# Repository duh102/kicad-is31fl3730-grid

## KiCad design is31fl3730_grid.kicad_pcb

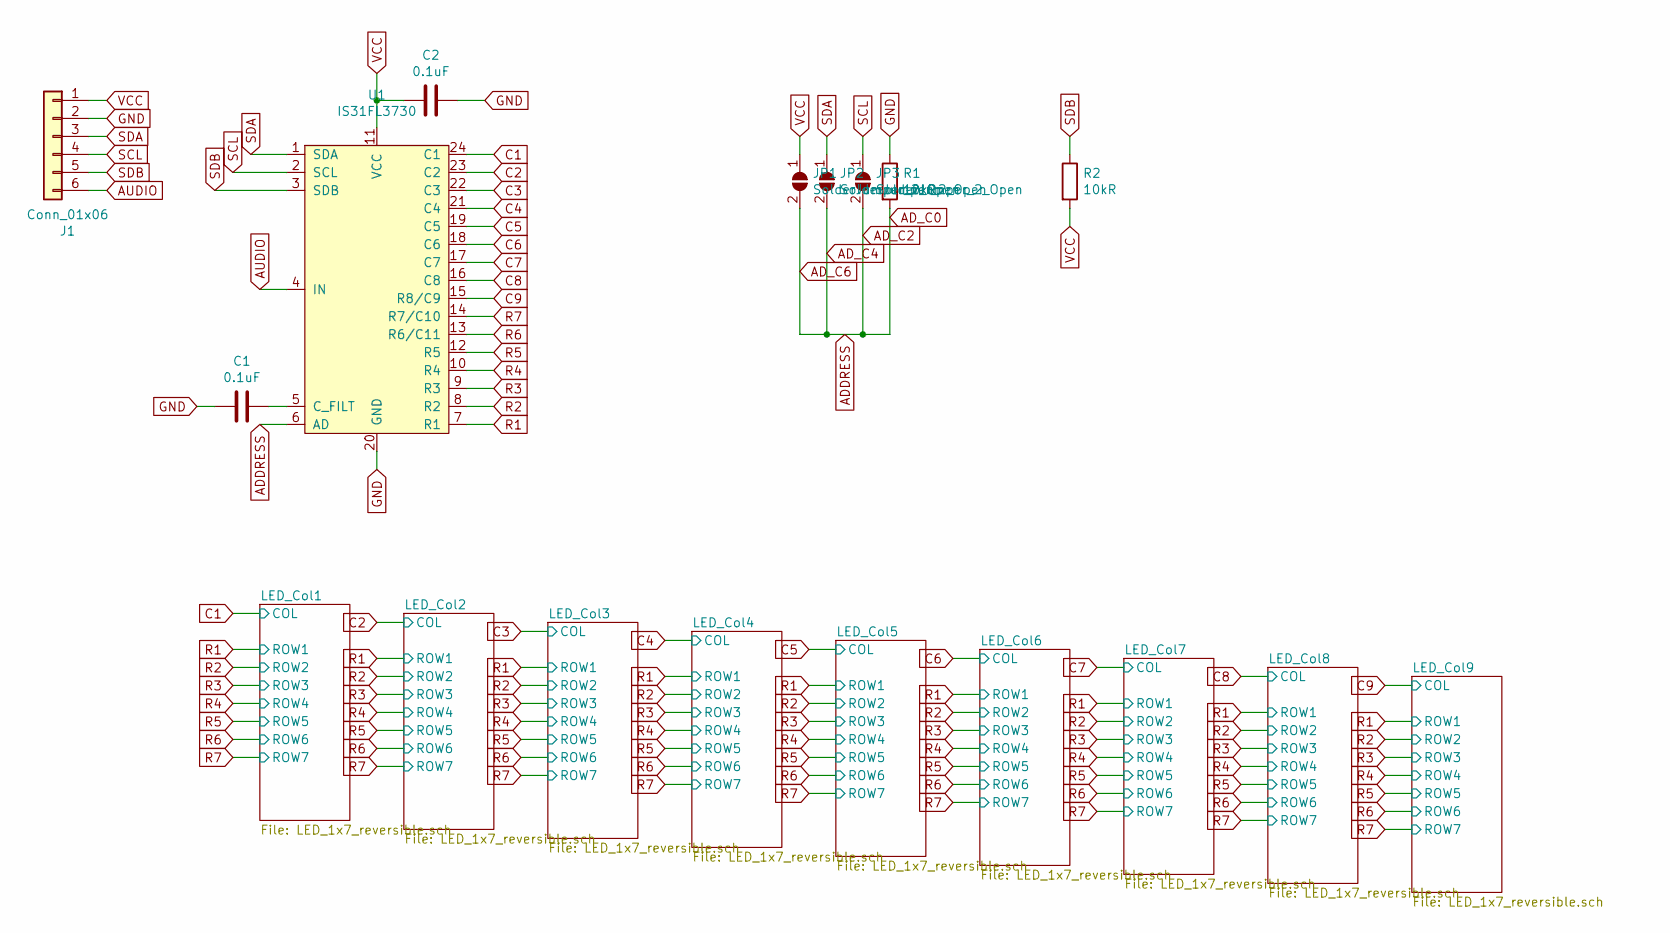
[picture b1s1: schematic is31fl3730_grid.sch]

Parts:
C1, C2: 0.1uF; C_0603_1608Metric
J1: Conn_01x06; PinHeader_1x06_P2.54mm_Vertical
JP1, JP2, JP3: SolderJumper_2_Open; SolderJumper-2_P1.3mm_Open_TrianglePad1.0x1.5mm
R1, R2: 10kR; R_0805_2012Metric
U1: IS31FL3730; QFN-24-1EP_4x4mm_P0.5mm_EP2.8x2.8mm

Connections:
ADDRESS: JP1.2 (B), JP2.2 (B), JP3.2 (B), R1.2, U1.6 (AD)
AUDIO: J1.6, U1.4 (IN)
C1: U1.24 (C1); also elsewhere on the board
C2: U1.23 (C2); also elsewhere on the board
C3: U1.22 (C3); also elsewhere on the board
C4: U1.21 (C4); also elsewhere on the board
C5: U1.19 (C5); also elsewhere on the board
C6: U1.18 (C6); also elsewhere on the board
C7: U1.17 (C7); also elsewhere on the board
C8: U1.16 (C8); also elsewhere on the board
C9: U1.15 (R8/C9); also elsewhere on the board
GND: C1.2, C2.1, J1.2, R1.1, U1.20 (GND)
unnamed: C1.1, U1.5 (C_FILT)
R1: U1.7 (R1); also elsewhere on the board
R2: U1.8 (R2); also elsewhere on the board
R3: U1.9 (R3); also elsewhere on the board
R4: U1.10 (R4); also elsewhere on the board
R5: U1.12 (R5); also elsewhere on the board
R6: U1.13 (R6/C11); also elsewhere on the board
R7: U1.14 (R7/C10); also elsewhere on the board
SCL: J1.4, JP3.1 (A), U1.2 (SCL)
SDA: J1.3, JP2.1 (A), U1.1 (SDA)
SDB: J1.5, R2.1, U1.3 (SDB)
VCC: C2.2, J1.1, JP1.1 (A), R2.2, U1.11 (VCC)

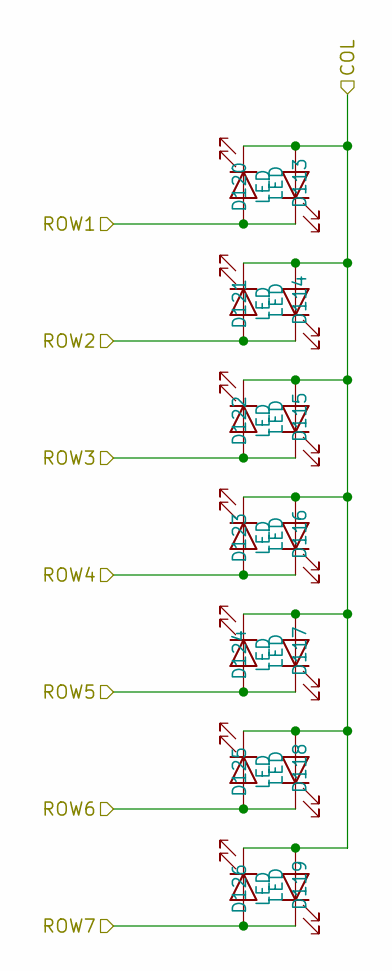
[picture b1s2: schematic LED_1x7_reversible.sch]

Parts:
D1, D2, D3, D4, D5, D6, D7, D8, D9, D10, D11, D12, D13, D14: LED; LED_0805_2012Metric

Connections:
C1: D1.1 (K), D2.1 (K), D3.1 (K), D4.1 (K), D5.1 (K), D6.1 (K), D7.1 (K), D8.2 (A), D9.2 (A), D10.2 (A), D11.2 (A), D12.2 (A), D13.2 (A), D14.2 (A); also elsewhere on the board
R1: D1.2 (A), D8.1 (K); also elsewhere on the board
R2: D2.2 (A), D9.1 (K); also elsewhere on the board
R3: D3.2 (A), D10.1 (K); also elsewhere on the board
R4: D4.2 (A), D11.1 (K); also elsewhere on the board
R5: D5.2 (A), D12.1 (K); also elsewhere on the board
R6: D6.2 (A), D13.1 (K); also elsewhere on the board
R7: D7.2 (A), D14.1 (K); also elsewhere on the board

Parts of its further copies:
D15, D16, D17, D18, D19, D20, D21, D22, D23, D24, D25, D26, D27, D28, D29, D30, D31, D32, D33, D34, D35, D36, D37, D38, D39, D40, D41, D42, D43, D44, D45, D46, D47, D48, D49, D50, D51, D52, D53, D54, D55, D56, D57, D58, D59, D60, D61, D62, D63, D64, D65, D66, D67, D68, D69, D70, D71, D72, D73, D74, D75, D76, D77, D78, D79, D80, D81, D82, D83, D84, D85, D86, D87, D88, D89, D90, D91, D92, D93, D94, D95, D96, D97, D98, D99, D100, D101, D102, D103, D104, D105, D106, D107, D108, D109, D110, D111, D112, D113, D114, D115, D116, D117, D118, D119, D120, D121, D122, D123, D124, D125, D126: LED; LED_0805_2012Metric

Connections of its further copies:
C2: D15.1 (K), D16.1 (K), D17.1 (K), D18.1 (K), D19.1 (K), D20.1 (K), D21.1 (K), D22.2 (A), D23.2 (A), D24.2 (A), D25.2 (A), D26.2 (A), D27.2 (A), D28.2 (A); also elsewhere on the board
C3: D29.1 (K), D30.1 (K), D31.1 (K), D32.1 (K), D33.1 (K), D34.1 (K), D35.1 (K), D36.2 (A), D37.2 (A), D38.2 (A), D39.2 (A), D40.2 (A), D41.2 (A), D42.2 (A); also elsewhere on the board
C4: D43.1 (K), D44.1 (K), D45.1 (K), D46.1 (K), D47.1 (K), D48.1 (K), D49.1 (K), D50.2 (A), D51.2 (A), D52.2 (A), D53.2 (A), D54.2 (A), D55.2 (A), D56.2 (A); also elsewhere on the board
C5: D57.1 (K), D58.1 (K), D59.1 (K), D60.1 (K), D61.1 (K), D62.1 (K), D63.1 (K), D64.2 (A), D65.2 (A), D66.2 (A), D67.2 (A), D68.2 (A), D69.2 (A), D70.2 (A); also elsewhere on the board
C6: D71.1 (K), D72.1 (K), D73.1 (K), D74.1 (K), D75.1 (K), D76.1 (K), D77.1 (K), D78.2 (A), D79.2 (A), D80.2 (A), D81.2 (A), D82.2 (A), D83.2 (A), D84.2 (A); also elsewhere on the board
C7: D85.1 (K), D86.1 (K), D87.1 (K), D88.1 (K), D89.1 (K), D90.1 (K), D91.1 (K), D92.2 (A), D93.2 (A), D94.2 (A), D95.2 (A), D96.2 (A), D97.2 (A), D98.2 (A); also elsewhere on the board
C8: D99.1 (K), D100.1 (K), D101.1 (K), D102.1 (K), D103.1 (K), D104.1 (K), D105.1 (K), D106.2 (A), D107.2 (A), D108.2 (A), D109.2 (A), D110.2 (A), D111.2 (A), D112.2 (A); also elsewhere on the board
C9: D113.1 (K), D114.1 (K), D115.1 (K), D116.1 (K), D117.1 (K), D118.1 (K), D119.1 (K), D120.2 (A), D121.2 (A), D122.2 (A), D123.2 (A), D124.2 (A), D125.2 (A), D126.2 (A); also elsewhere on the board
R1: D15.2 (A), D22.1 (K), D29.2 (A), D36.1 (K), D43.2 (A), D50.1 (K), D57.2 (A), D64.1 (K), D71.2 (A), D78.1 (K), D85.2 (A), D92.1 (K), D99.2 (A), D106.1 (K), D113.2 (A), D120.1 (K); also elsewhere on the board
R2: D16.2 (A), D23.1 (K), D30.2 (A), D37.1 (K), D44.2 (A), D51.1 (K), D58.2 (A), D65.1 (K), D72.2 (A), D79.1 (K), D86.2 (A), D93.1 (K), D100.2 (A), D107.1 (K), D114.2 (A), D121.1 (K); also elsewhere on the board
R3: D17.2 (A), D24.1 (K), D31.2 (A), D38.1 (K), D45.2 (A), D52.1 (K), D59.2 (A), D66.1 (K), D73.2 (A), D80.1 (K), D87.2 (A), D94.1 (K), D101.2 (A), D108.1 (K), D115.2 (A), D122.1 (K); also elsewhere on the board
R4: D18.2 (A), D25.1 (K), D32.2 (A), D39.1 (K), D46.2 (A), D53.1 (K), D60.2 (A), D67.1 (K), D74.2 (A), D81.1 (K), D88.2 (A), D95.1 (K), D102.2 (A), D109.1 (K), D116.2 (A), D123.1 (K); also elsewhere on the board
R5: D19.2 (A), D26.1 (K), D33.2 (A), D40.1 (K), D47.2 (A), D54.1 (K), D61.2 (A), D68.1 (K), D75.2 (A), D82.1 (K), D89.2 (A), D96.1 (K), D103.2 (A), D110.1 (K), D117.2 (A), D124.1 (K); also elsewhere on the board
R6: D20.2 (A), D27.1 (K), D34.2 (A), D41.1 (K), D48.2 (A), D55.1 (K), D62.2 (A), D69.1 (K), D76.2 (A), D83.1 (K), D90.2 (A), D97.1 (K), D104.2 (A), D111.1 (K), D118.2 (A), D125.1 (K); also elsewhere on the board
R7: D21.2 (A), D28.1 (K), D35.2 (A), D42.1 (K), D49.2 (A), D56.1 (K), D63.2 (A), D70.1 (K), D77.2 (A), D84.1 (K), D91.2 (A), D98.1 (K), D105.2 (A), D112.1 (K), D119.2 (A), D126.1 (K); also elsewhere on the board

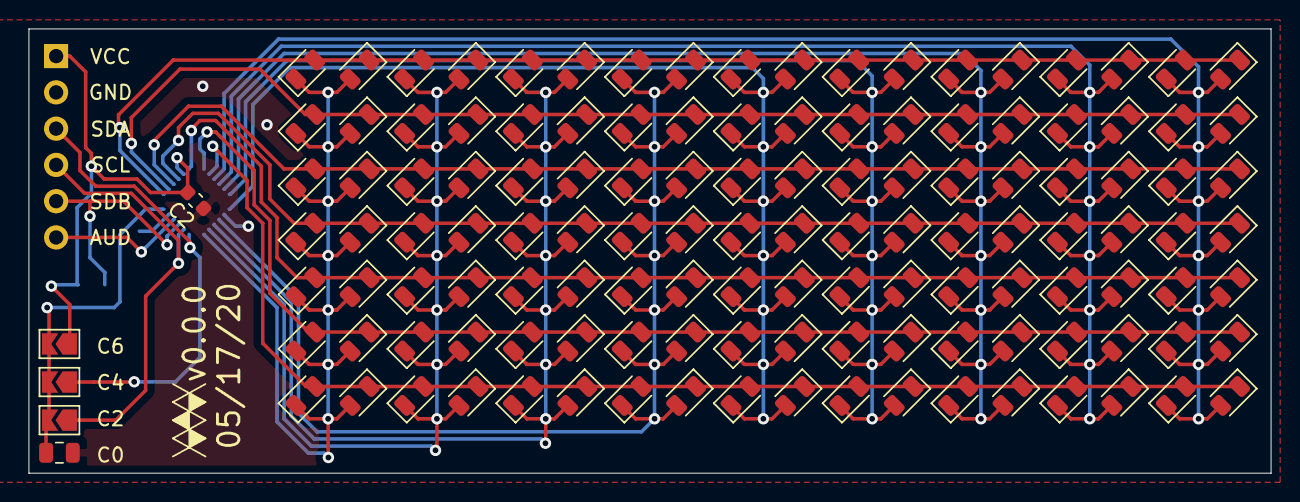
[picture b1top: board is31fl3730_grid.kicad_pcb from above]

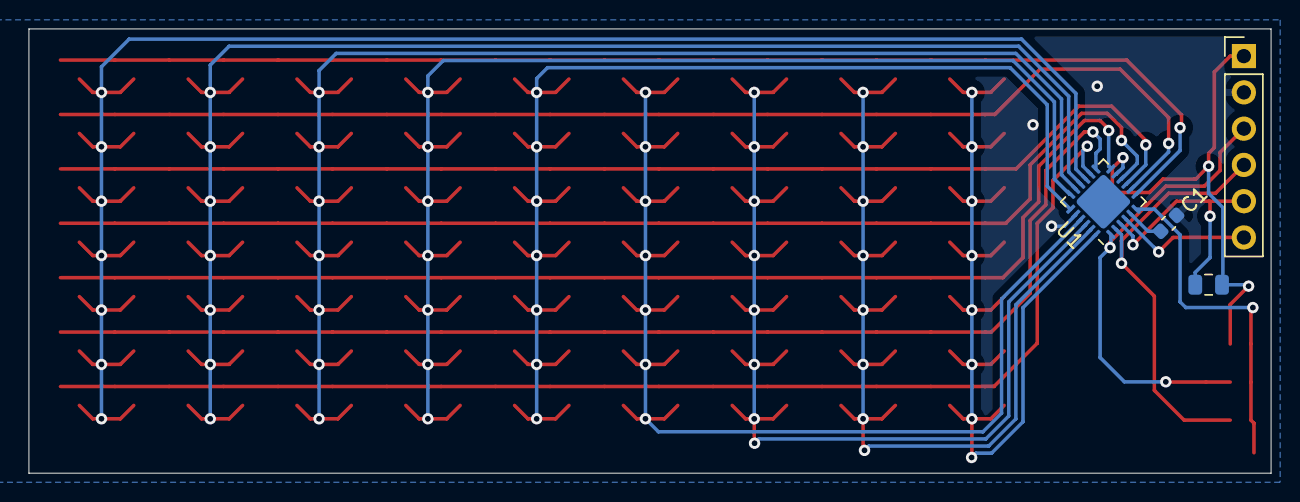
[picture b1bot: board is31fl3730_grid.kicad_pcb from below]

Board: 2 copper layers, 87.0 x 31.1 mm, 135 parts (4 on the bottom side), 24 nets.

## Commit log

2020-05-17 Initial commit, just schematic
2020-05-17 Placed 14x9 grid
2020-05-18 Fix matrix
2020-12-09 Rescue libs
